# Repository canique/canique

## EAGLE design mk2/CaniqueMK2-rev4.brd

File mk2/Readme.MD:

# Canique MK2 Schematics

These are schematics for Canique MK2 rev4 based on https://github.com/LowPowerLab/Moteino/tree/master/R4 from Felix Rusu.
Some noteable changes on the MK2 board are: The RFM69 has additional capacitors on the back of the board, the trace routing is different, the FTDI connector circumvents the voltage regulator.

# License
CC-BY-SA 4.0 https://creativecommons.org/licenses/by-sa/4.0/
You are free to share and adapt. But you need to give attribution and use the same license to redistribute.

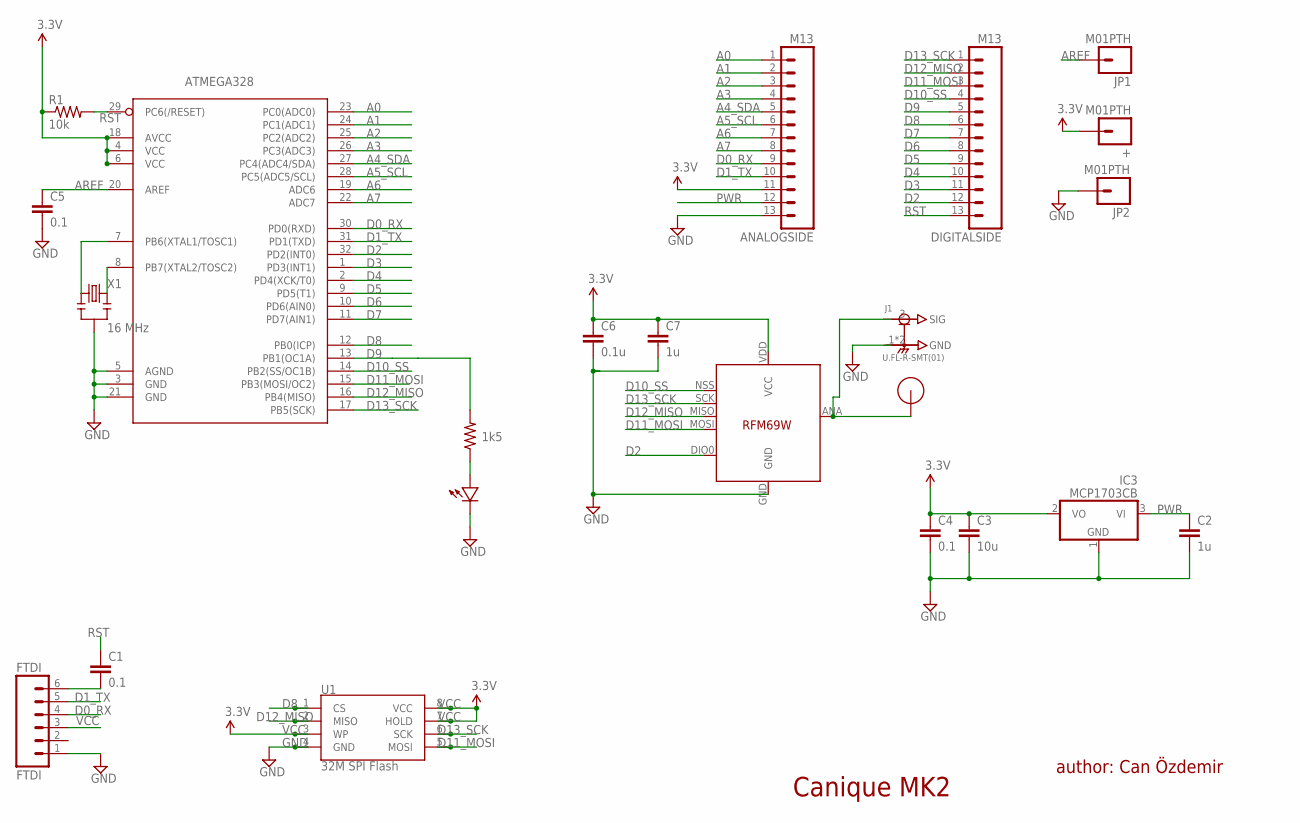
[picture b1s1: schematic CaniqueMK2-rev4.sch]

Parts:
+: M01PTH; 1X01
ANALOGSIDE: M13; 1X13
ATMEGA328: ATMega-328; TQFP32-08
C1, C4, C5: 0.1; 0603-CAP
C2, C7: 1u; 0603-CAP
C3: 10u; 0805-CAP
C6: 0.1u; 0603-CAP
DIGITALSIDE: M13; 1X13
FTDI: FTDI; 1X06
IC3: MCP1703CB; SOT23
J1: U.FL-R-SMT(01); HRS_U.FL-R-SMT(01)
JP1, JP2: M01PTH; 1X01
R1: 10k; 0603-RES
R2: 1k5; 0603-RES
U1: 32M SPI Flash; SO08
U$1: RFM12B_ANTENNA; RFM12B-ANTENNA
U$2: LED0603; 0603-LED
U$5: RFM69; RFM69W-MINPADS
X1: 16 MHz; RESONATOR-SMD

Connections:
A0: ANALOGSIDE.1, ATMEGA328.23 (PC0(ADC0))
A1: ANALOGSIDE.2, ATMEGA328.24 (PC1(ADC1))
A2: ANALOGSIDE.3, ATMEGA328.25 (PC2(ADC2))
A3: ANALOGSIDE.4, ATMEGA328.26 (PC3(ADC3))
A4_SDA: ANALOGSIDE.5, ATMEGA328.27 (PC4(ADC4/SDA))
A5_SCL: ANALOGSIDE.6, ATMEGA328.28 (PC5(ADC5/SCL))
A6: ANALOGSIDE.7, ATMEGA328.19 (ADC6)
A7: ANALOGSIDE.8, ATMEGA328.22 (ADC7)
AREF: ATMEGA328.20 (AREF), C5.1, JP1.1
D0_RX: ANALOGSIDE.9, ATMEGA328.30 (PD0(RXD)), FTDI.4
D1_TX: ANALOGSIDE.10, ATMEGA328.31 (PD1(TXD)), FTDI.5
D2: ATMEGA328.32 (PD2(INT0)), DIGITALSIDE.12, U$5.DIO0
D3: ATMEGA328.1 (PD3(INT1)), DIGITALSIDE.11
D4: ATMEGA328.2 (PD4(XCK/T0)), DIGITALSIDE.10
D5: ATMEGA328.9 (PD5(T1)), DIGITALSIDE.9
D6: ATMEGA328.10 (PD6(AIN0)), DIGITALSIDE.8
D7: ATMEGA328.11 (PD7(AIN1)), DIGITALSIDE.7
D8: ATMEGA328.12 (PB0(ICP)), DIGITALSIDE.6, U1.1 (CS)
D9: ATMEGA328.13 (PB1(OC1A)), DIGITALSIDE.5, R2.2
D10_SS: ATMEGA328.14 (PB2(SS/OC1B)), DIGITALSIDE.4, U$5.NSS (SEL)
D11_MOSI: ATMEGA328.15 (PB3(MOSI/OC2)), DIGITALSIDE.3, U1.5 (MOSI), U$5.MOSI
D12_MISO: ATMEGA328.16 (PB4(MISO)), DIGITALSIDE.2, U1.2 (MISO), U$5.MISO
D13_SCK: ATMEGA328.17 (PB5(SCK)), DIGITALSIDE.1, U1.6 (SCK), U$5.SCK
GND: ANALOGSIDE.13, ATMEGA328.3 (GND), ATMEGA328.5 (AGND), ATMEGA328.21 (GND), C2.2, C3.2, C4.2, C5.2, C6.2, C7.2, FTDI.1, IC3.1 (GND), J1.1 (GND), J1.2 (GND), JP2.1, U1.4 (GND), U$2.MINUS, U$5.GND, X1.2
unnamed: ATMEGA328.7 (PB6(XTAL1/TOSC1)), X1.1
unnamed: R2.1, U$2.PLUS
unnamed: J1.3 (SIG), U$1.P$1, U$5.ANA (ANT)
unnamed: C1.2, FTDI.6
unnamed: ATMEGA328.8 (PB7(XTAL2/TOSC2)), X1.3
PWR: ANALOGSIDE.12, C2.1, IC3.3 (VI)
RST: ATMEGA328.29 (PC6(/RESET)), C1.1, DIGITALSIDE.13, R1.2
VCC: +.1, ANALOGSIDE.11, ATMEGA328.4 (VCC), ATMEGA328.6 (VCC), ATMEGA328.18 (AVCC), C3.1, C4.1, C6.1, C7.1, FTDI.3, IC3.2 (VO), R1.1, U1.3 (WP), U1.7 (HOLD), U1.8 (VCC), U$5.VDD (VCC)

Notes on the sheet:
Canique MK2
author: Can Özdemir

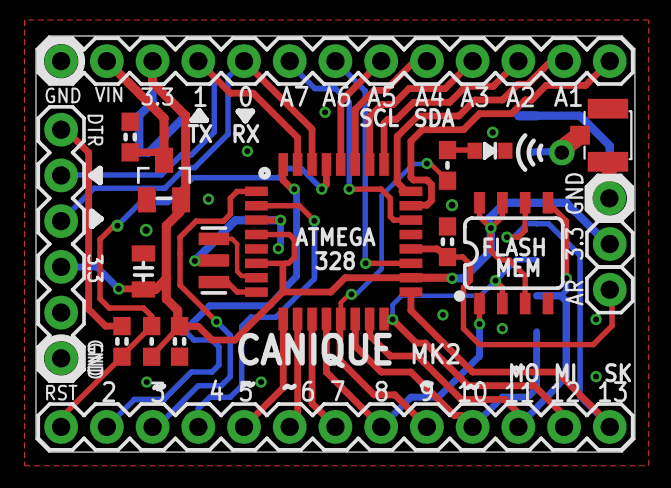
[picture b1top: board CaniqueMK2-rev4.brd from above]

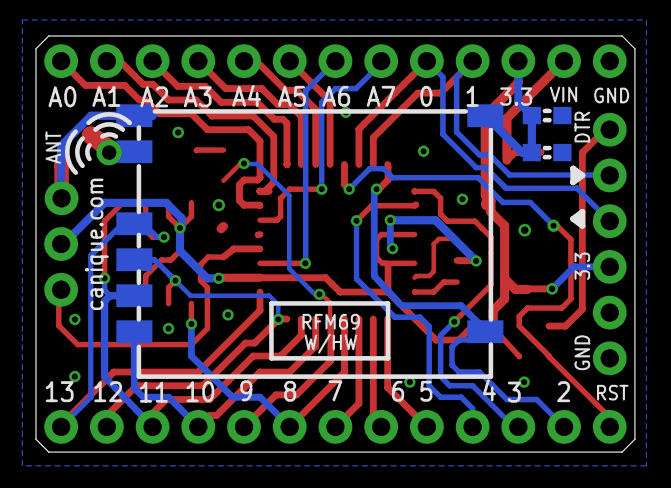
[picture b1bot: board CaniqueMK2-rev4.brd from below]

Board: 2 copper layers, 33.3 x 23.1 mm, 23 parts (3 on the bottom side), 32 nets.

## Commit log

2018-02-03 Create battery_measurement.ino
    Used to demonstrate how to measure battery voltage with a Canique ULV board.
2018-02-04 Update battery_measurement.ino
    added comment
2018-02-04 Update battery_measurement.ino
    fixed error with BATTERY_VOLTAGE_PRESCALER
    put a delay after switching voltage reference
    discard readings that are interrupted by any other interrupt than the ADC interrupt
2018-02-28 Update battery_measurement.ino
    Fixed power consumption issues with ADC in low power mode.
2018-08-20 MK3e test sketches to test RFM95/96 connectivity
2023-02-22 mk2 rev4 schematics

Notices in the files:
parts and their libraries:
SparkFun-Connectors: Licensing: CC v3.0 Share-Alike You are welcome to use this library for commercial purposes.
SparkFun-IC-Memory: Licensing: Creative Commons ShareAlike 4.0 International - https://creativecommons.org/licenses/by-sa/4.0
